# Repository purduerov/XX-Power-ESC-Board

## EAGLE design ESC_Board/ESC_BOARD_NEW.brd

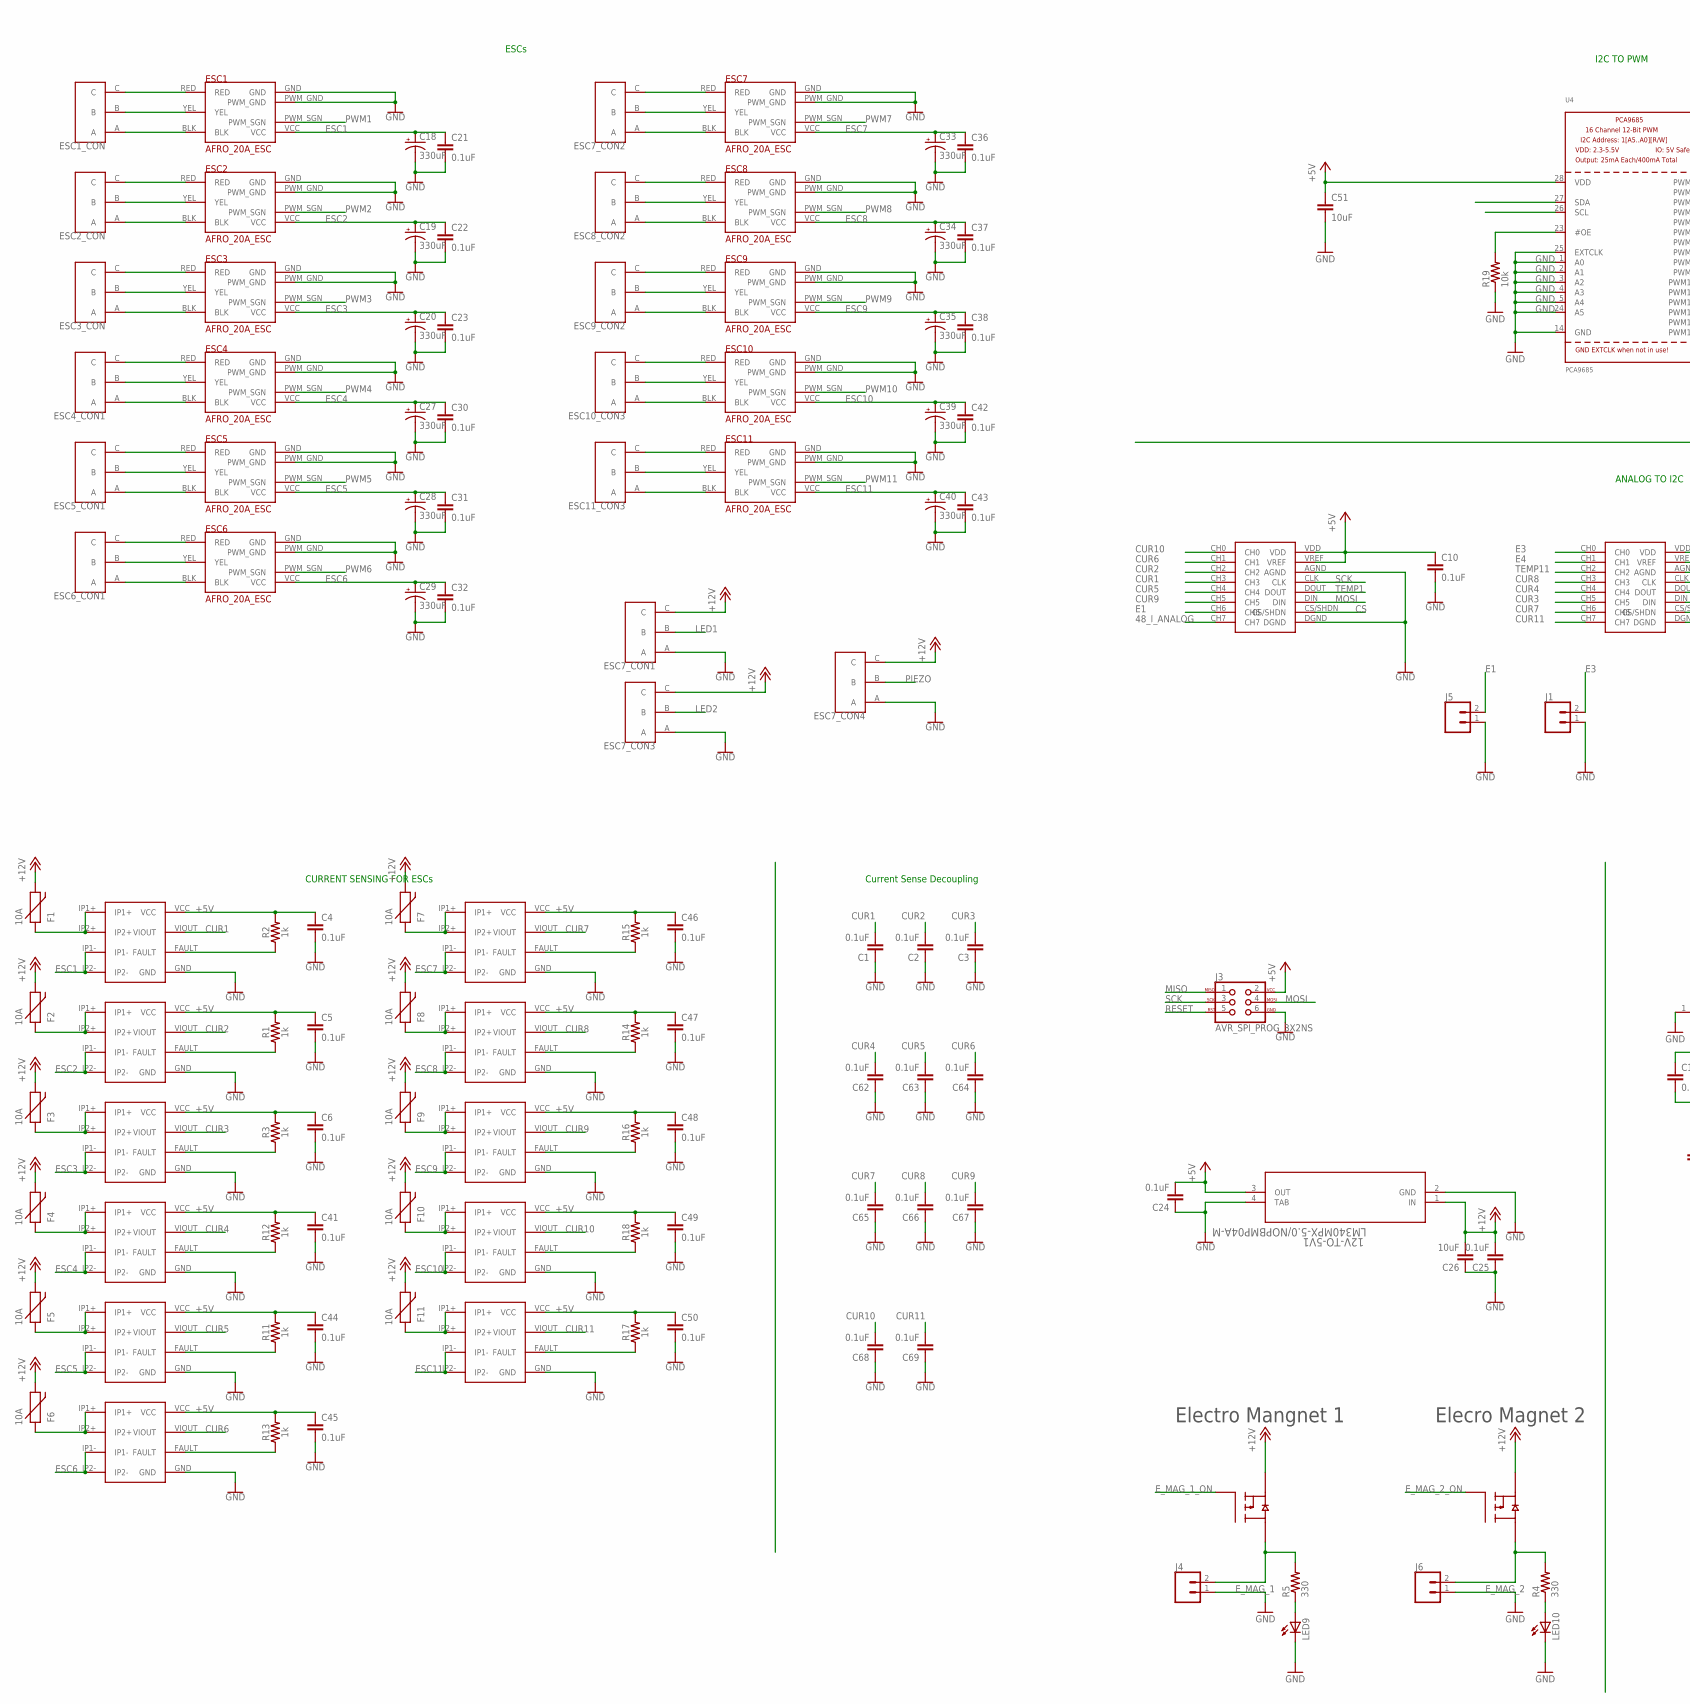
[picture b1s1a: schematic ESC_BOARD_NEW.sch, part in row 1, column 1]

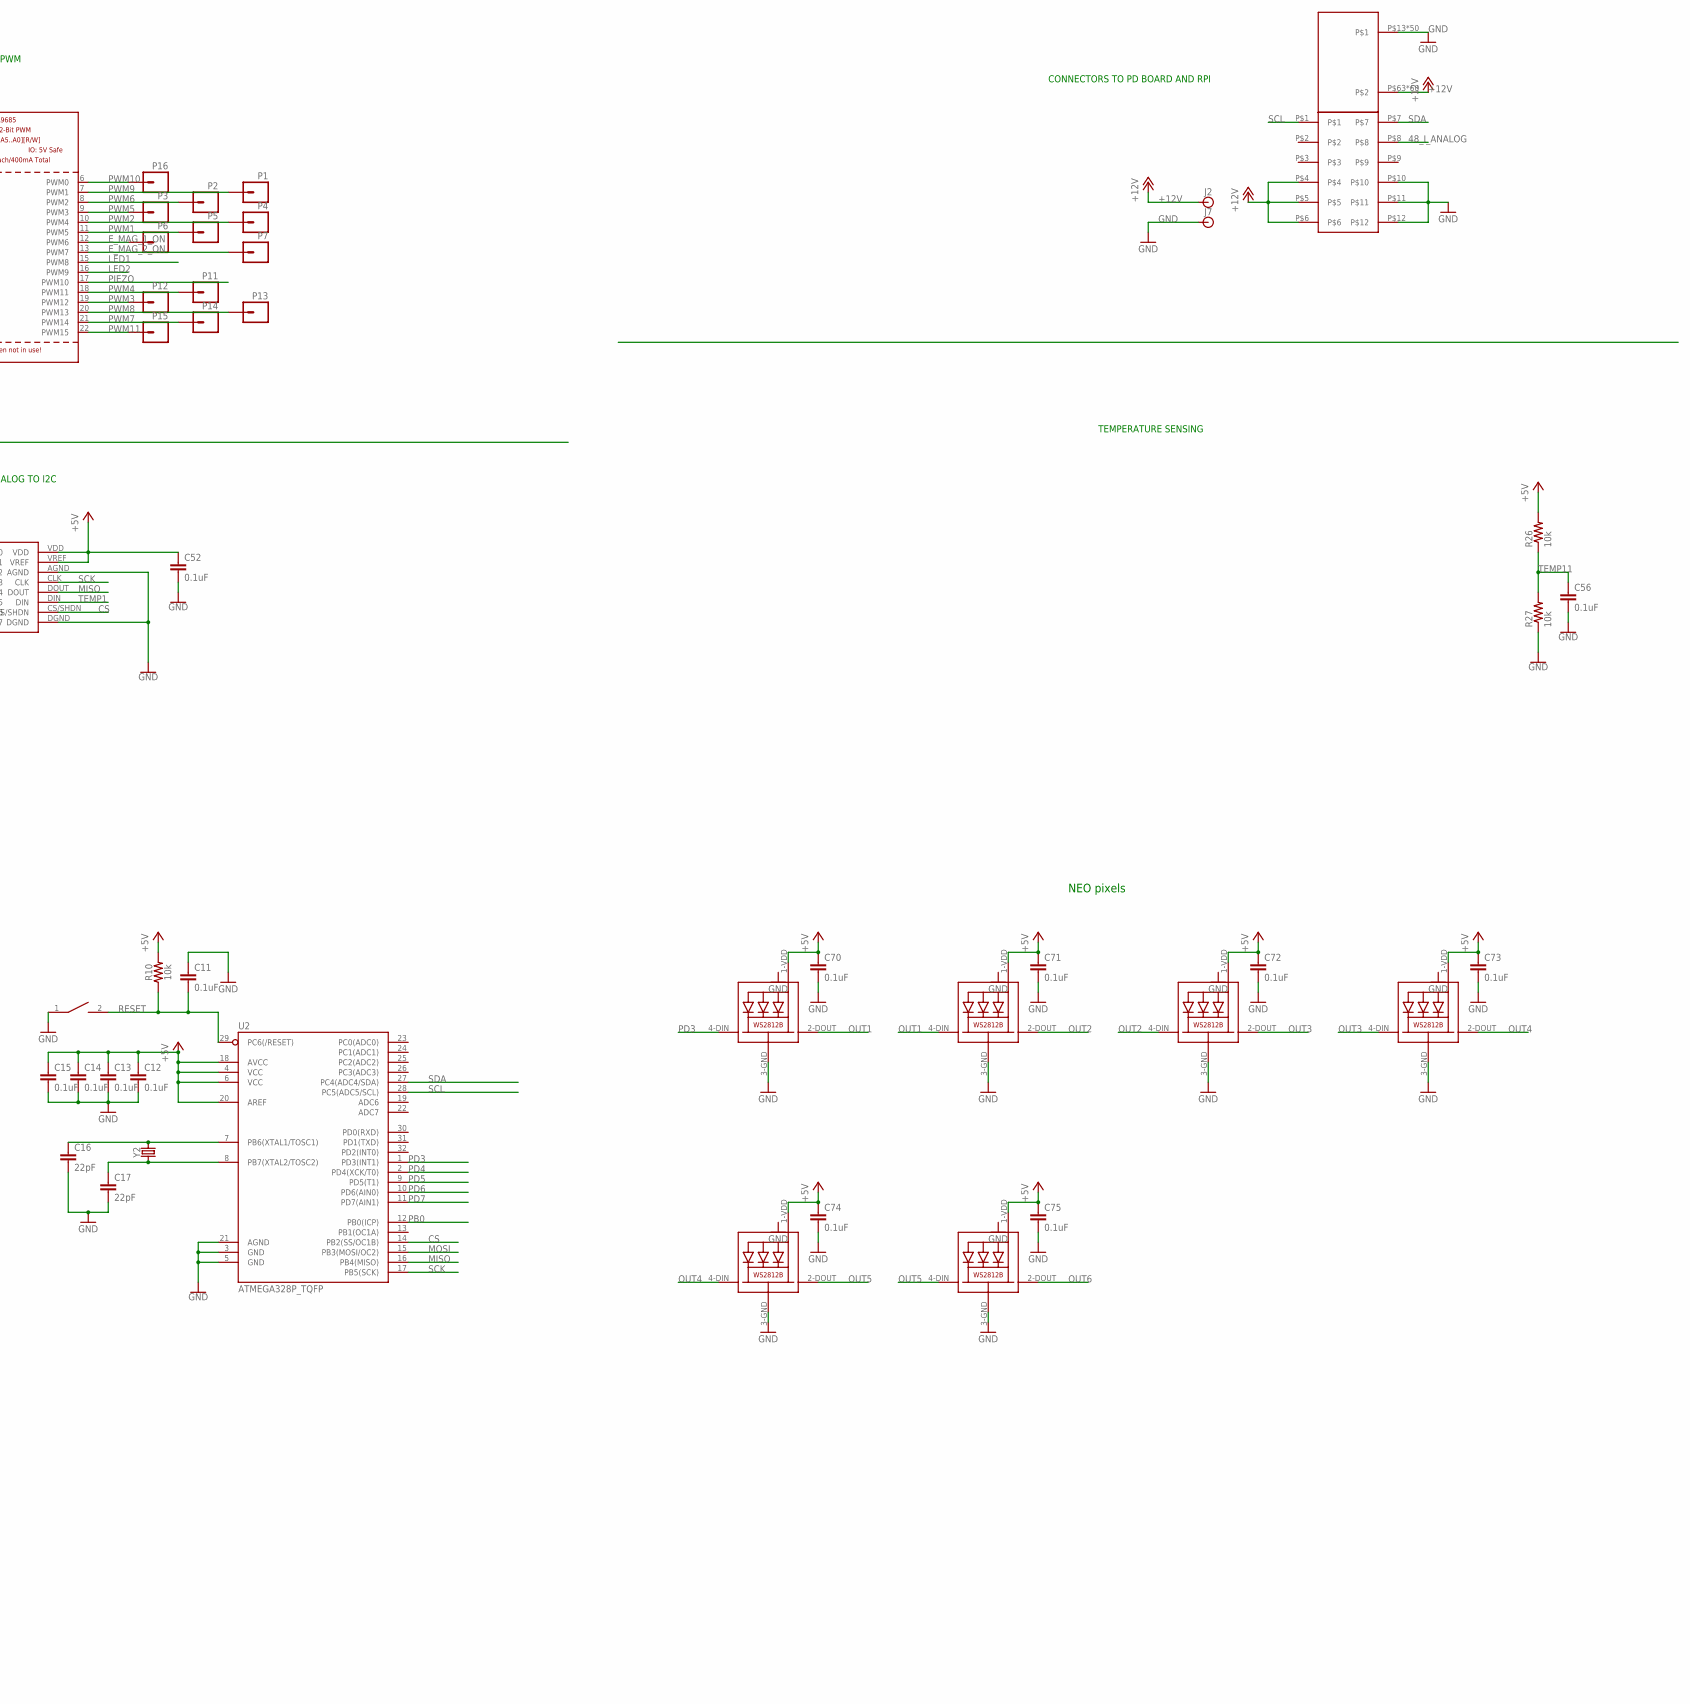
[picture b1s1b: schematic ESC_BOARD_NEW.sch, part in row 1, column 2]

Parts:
12V-TO-5V1: LM340MPX-5.0/NOPBMP04A-M; MP04A-M
C1, C2, C3, C4, C5, C6, C10, C21, C22, C23, C24, C25, C30, C31, C32, C36, C37, C38, C41, C42, C43, C44, C45, C46, C47, C48, C49, C50, C52, C56, C62, C63, C64, C65, C66, C67, C68, C69: 0.1uF; 0603
C11, C12, C13, C14, C15, C70, C71, C72, C73, C74, C75: 0.1uF; C0603
C16, C17: 22pF; C0603
C18, C19, C20, C27, C28, C29, C33, C34, C35, C39, C40: 330uF; CPOL-US(10.3_10.3MM)
C26: 10uF; 0603
C51: 10uF; 0603-CAP
ESC1, ESC2, ESC3, ESC4, ESC5, ESC6, ESC7, ESC8, ESC9, ESC10, ESC11: AFRO_20A_ESC
ESC1_CON, ESC2_CON, ESC3_CON, ESC4_CON1, ESC5_CON1, ESC6_CON1, ESC7_CON1, ESC7_CON2, ESC7_CON3, ESC7_CON4, ESC8_CON2, ESC9_CON2, ESC10_CON3, ESC11_CON3: 3PINCONNECTOR
F1, F2, F3, F4, F5, F6, F7, F8, F9, F10, F11: 10A; PTC-2920
J1, J4, J5, J6: CONN_02; 1X02
J2, J7: BANANA_CONN
J3: AVR_SPI_PROG_3X2NS; 2X3-NS
LED1, LED2, LED3, LED4, LED5, LED6: WS2812B5050; WS2812B
LED9, LED10: LEDSML0603; SML0603
P1, P2, P3, P4, P5, P6, P7, P11, P12, P13, P14, P15, P16: M01PTH; 1X01
R1, R2, R3, R11, R12, R13, R14, R15, R16, R17, R18: 1k; 0603
R4, R5: 330; R0603
R10: 10k; 0603
R19: 10k; 0603-RES
R26, R27: 10k; R0603
RESET: SWITCH; SW_2512
U1, U3: FQB27P06; TO263-3
U2: ATMEGA328P_TQFP; TQFP32-08
U4: PCA9685; TSSOP28
U$1, U$2, U$3, U$5, U$6, U$7, U$8, U$9, U$10, U$11, U$12: ACS711
U$4, U$13: MCP3008
U$15: ESC-FULL
Y2: CRYSTALPTH-HC49US; HC49US

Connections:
48_I_ANALOG: U$4.CH7, U$15.P$8
+5V: 12V-TO-5V1.3 (OUT), C4.1, C5.1, C6.1, C10.1, C12.1, C13.1, C14.1, C15.1, C24.2, C41.1, C44.1, C45.1, C46.1, C47.1, C48.1, C49.1, C50.1, C51.1, C52.1, C70.1, C71.1, C72.1, C73.1, C74.1, C75.1, J3.2, LED1.1-VDD (VDD), LED2.1-VDD (VDD), LED3.1-VDD (VDD), LED4.1-VDD (VDD), LED5.1-VDD (VDD), LED6.1-VDD (VDD), R1.2, R2.2, R3.2, R10.2, R11.2, R12.2, R13.2, R14.2, R15.2, R16.2, R17.2, R18.2, R26.2, U2.4 (VCC), U2.6 (VCC), U2.18 (AVCC), U2.20 (AREF), U4.28 (VDD), U$1.VCC, U$2.VCC, U$3.VCC, U$4.VDD, U$4.VREF, U$5.VCC, U$6.VCC, U$7.VCC, U$8.VCC, U$9.VCC, U$10.VCC, U$11.VCC, U$12.VCC, U$13.VDD, U$13.VREF
+12V: 12V-TO-5V1.1 (IN), C25.2, C26.2, ESC7_CON1.C, ESC7_CON3.C, ESC7_CON4.C, F1.2, F2.2, F3.2, F4.2, F5.2, F6.2, F7.2, F8.2, F9.2, F10.2, F11.2, J2.P$1, U1.3 (S2), U3.3 (S2), U$15.P$4, U$15.P$5, U$15.P$6, U$15.P$63, U$15.P$64, U$15.P$65, U$15.P$66, U$15.P$67, U$15.P$68, U$15.P$69, U$15.P$70, U$15.P$71, U$15.P$72, U$15.P$73, U$15.P$74, U$15.P$75, U$15.P$76, U$15.P$77, U$15.P$78, U$15.P$79, U$15.P$80, U$15.P$81, U$15.P$82, U$15.P$83, U$15.P$84, U$15.P$85, U$15.P$86, U$15.P$87, U$15.P$88, U$15.P$89, U$15.P$90, U$15.P$91, U$15.P$92, U$15.P$101, U$15.P$102, U$15.P$103, U$15.P$104, U$15.P$105, U$15.P$106, U$15.P$107, U$15.P$108, U$15.P$109, U$15.P$110, U$15.P$111, U$15.P$112, U$15.P$113, U$15.P$114, U$15.P$115, U$15.P$116, U$15.P$117, U$15.P$118, U$15.P$119, U$15.P$120, U$15.P$121, U$15.P$122, U$15.P$123, U$15.P$124, U$15.P$125, U$15.P$126, U$15.P$127, U$15.P$128, U$15.P$129, U$15.P$130
CS: U2.14 (PB2(SS/OC1B)), U$4.CS/SHDN, U$13.CS/SHDN
CUR1: C1.2, U$1.VIOUT, U$4.CH3
CUR2: C2.2, U$2.VIOUT, U$4.CH2
CUR3: C3.2, U$3.VIOUT, U$13.CH5
CUR4: C62.2, U$5.VIOUT, U$13.CH4
CUR5: C63.2, U$4.CH4, U$6.VIOUT
CUR6: C64.2, U$4.CH1, U$7.VIOUT
CUR7: C65.2, U$8.VIOUT, U$13.CH6
CUR8: C66.2, U$9.VIOUT, U$13.CH3
CUR9: C67.2, U$4.CH5, U$10.VIOUT
CUR10: C68.2, U$4.CH0, U$11.VIOUT
CUR11: C69.2, U$12.VIOUT, U$13.CH7
E1: J5.2, U$4.CH6
E3: J1.2, U$13.CH0
E4: U$13.CH1
ESC1: C18.+, C21.1, ESC1.VCC, U$1.IP1-, U$1.IP2-
ESC2: C19.+, C22.1, ESC2.VCC, U$2.IP1-, U$2.IP2-
ESC3: C20.+, C23.1, ESC3.VCC, U$3.IP1-, U$3.IP2-
ESC4: C27.+, C30.1, ESC4.VCC, U$5.IP1-, U$5.IP2-
ESC5: C28.+, C31.1, ESC5.VCC, U$6.IP1-, U$6.IP2-
ESC6: C29.+, C32.1, ESC6.VCC, U$7.IP1-, U$7.IP2-
ESC7: C33.+, C36.1, ESC7.VCC, U$8.IP1-, U$8.IP2-
ESC8: C34.+, C37.1, ESC8.VCC, U$9.IP1-, U$9.IP2-
ESC9: C35.+, C38.1, ESC9.VCC, U$10.IP1-, U$10.IP2-
ESC10: C39.+, C42.1, ESC10.VCC, U$11.IP1-, U$11.IP2-
ESC11: C40.+, C43.1, ESC11.VCC, U$12.IP1-, U$12.IP2-
E_MAG_1: J4.2, R5.2, U1.TAB (D2)
E_MAG_1_ON: P6.1, U1.1 (G2), U4.12 (PWM6)
E_MAG_2: J6.2, R4.2, U3.TAB (D2)
E_MAG_2_ON: P7.1, U3.1 (G2), U4.13 (PWM7)
GND: 12V-TO-5V1.2 (GND), 12V-TO-5V1.4 (TAB), C1.1, C2.1, C3.1, C4.2, C5.2, C6.2, C10.2, C11.1, C12.2, C13.2, C14.2, C15.2, C16.2, C17.2, C18.-, C19.-, C20.-, C21.2, C22.2, C23.2, C24.1, C25.1, C26.1, C27.-, C28.-, C29.-, C30.2, C31.2, C32.2, C33.-, C34.-, C35.-, C36.2, C37.2, C38.2, C39.-, C40.-, C41.2, C42.2, C43.2, C44.2, C45.2, C46.2, C47.2, C48.2, C49.2, C50.2, C51.2, C52.2, C56.2, C62.1, C63.1, C64.1, C65.1, C66.1, C67.1, C68.1, C69.1, C70.2, C71.2, C72.2, C73.2, C74.2, C75.2, ESC1.GND, ESC1.PWM_GND, ESC2.GND, ESC2.PWM_GND, ESC3.GND, ESC3.PWM_GND, ESC4.GND, ESC4.PWM_GND, ESC5.GND, ESC5.PWM_GND, ESC6.GND, ESC6.PWM_GND, ESC7.GND, ESC7.PWM_GND, ESC7_CON1.A, ESC7_CON3.A, ESC7_CON4.A, ESC8.GND, ESC8.PWM_GND, ESC9.GND, ESC9.PWM_GND, ESC10.GND, ESC10.PWM_GND, ESC11.GND, ESC11.PWM_GND, J1.1, J3.6, J4.1, J5.1, J6.1, J7.P$1, LED1.3-GND (GND), LED2.3-GND (GND), LED3.3-GND (GND), LED4.3-GND (GND), LED5.3-GND (GND), LED6.3-GND (GND), LED9.C, LED10.C, R19.1, R27.1, RESET.1, U2.3 (GND), U2.5 (GND), U2.21 (AGND), U4.1 (A0), U4.2 (A1), U4.3 (A2), U4.4 (A3), U4.5 (A4), U4.14 (GND), U4.24 (A5), U4.25 (EXTCLK), U$1.GND, U$2.GND, U$3.GND, U$4.AGND, U$4.DGND, U$5.GND, U$6.GND, U$7.GND, U$8.GND, U$9.GND, U$10.GND, U$11.GND, U$12.GND, U$13.AGND, U$13.DGND, U$15.P$10, U$15.P$11, U$15.P$12, U$15.P$13, U$15.P$14, U$15.P$15, U$15.P$16, U$15.P$17, U$15.P$18, U$15.P$19, U$15.P$20, U$15.P$21, U$15.P$22, U$15.P$23, U$15.P$24, U$15.P$25, U$15.P$26, U$15.P$27, U$15.P$28, U$15.P$29, U$15.P$30, U$15.P$31, U$15.P$32, U$15.P$33, U$15.P$34, U$15.P$35, U$15.P$36, U$15.P$37, U$15.P$38, U$15.P$39, U$15.P$40, U$15.P$41, U$15.P$42, U$15.P$43, U$15.P$44, U$15.P$45, U$15.P$46, U$15.P$47, U$15.P$48, U$15.P$49, U$15.P$50, U$15.P$51, U$15.P$52, U$15.P$53, U$15.P$54, U$15.P$55, U$15.P$56, U$15.P$57, U$15.P$58, U$15.P$59, U$15.P$60, U$15.P$61, U$15.P$62
LED1: ESC7_CON1.B, U4.15 (PWM8)
LED2: ESC7_CON3.B, U4.16 (PWM9)
MISO: J3.1, U2.16 (PB4(MISO)), U$13.DOUT
MOSI: J3.4, U2.15 (PB3(MOSI/OC2)), U$4.DIN
unnamed: ESC2.RED, ESC2_CON.C
unnamed: R2.1, U$1.FAULT
unnamed: ESC2.YEL, ESC2_CON.B
unnamed: R1.1, U$2.FAULT
unnamed: ESC2.BLK, ESC2_CON.A
unnamed: R3.1, U$3.FAULT
unnamed: ESC1.RED, ESC1_CON.C
unnamed: ESC1.YEL, ESC1_CON.B
unnamed: ESC1.BLK, ESC1_CON.A
unnamed: ESC3.RED, ESC3_CON.C
unnamed: ESC3.YEL, ESC3_CON.B
unnamed: ESC3.BLK, ESC3_CON.A
unnamed: R12.1, U$5.FAULT
unnamed: C16.1, U2.7 (PB6(XTAL1/TOSC1)), Y2.2
unnamed: C17.1, U2.8 (PB7(XTAL2/TOSC2)), Y2.1
unnamed: ESC5.RED, ESC5_CON1.C
unnamed: ESC5.YEL, ESC5_CON1.B
unnamed: ESC5.BLK, ESC5_CON1.A
unnamed: ESC4.RED, ESC4_CON1.C
unnamed: ESC4.YEL, ESC4_CON1.B
unnamed: ESC4.BLK, ESC4_CON1.A
unnamed: ESC6.RED, ESC6_CON1.C
unnamed: ESC6.YEL, ESC6_CON1.B
unnamed: ESC6.BLK, ESC6_CON1.A
unnamed: ESC8.RED, ESC8_CON2.C
unnamed: ESC8.YEL, ESC8_CON2.B
unnamed: ESC8.BLK, ESC8_CON2.A
unnamed: ESC7.RED, ESC7_CON2.C
unnamed: ESC7.YEL, ESC7_CON2.B
unnamed: ESC7.BLK, ESC7_CON2.A
unnamed: ESC9.RED, ESC9_CON2.C
unnamed: ESC9.YEL, ESC9_CON2.B
unnamed: ESC9.BLK, ESC9_CON2.A
unnamed: ESC11.RED, ESC11_CON3.C
unnamed: ESC11.YEL, ESC11_CON3.B
unnamed: ESC11.BLK, ESC11_CON3.A
unnamed: ESC10.RED, ESC10_CON3.C
unnamed: ESC10.YEL, ESC10_CON3.B
unnamed: ESC10.BLK, ESC10_CON3.A
unnamed: R11.1, U$6.FAULT
unnamed: R13.1, U$7.FAULT
unnamed: R15.1, U$8.FAULT
unnamed: R14.1, U$9.FAULT
unnamed: R16.1, U$10.FAULT
unnamed: R18.1, U$11.FAULT
unnamed: R17.1, U$12.FAULT
unnamed: LED9.A, R5.1
unnamed: F6.1, U$7.IP1+, U$7.IP2+
unnamed: F1.1, U$1.IP1+, U$1.IP2+
unnamed: F2.1, U$2.IP1+, U$2.IP2+
unnamed: F3.1, U$3.IP1+, U$3.IP2+
unnamed: F4.1, U$5.IP1+, U$5.IP2+
unnamed: F5.1, U$6.IP1+, U$6.IP2+
unnamed: F7.1, U$8.IP1+, U$8.IP2+
unnamed: R19.2, U4.23 (#OE)
unnamed: F8.1, U$9.IP1+, U$9.IP2+
unnamed: F9.1, U$10.IP1+, U$10.IP2+
unnamed: F10.1, U$11.IP1+, U$11.IP2+
unnamed: F11.1, U$12.IP1+, U$12.IP2+
unnamed: LED10.A, R4.1
OUT1: LED1.2-DOUT (DO), LED2.4-DIN (DI)
OUT2: LED2.2-DOUT (DO), LED3.4-DIN (DI)
OUT3: LED3.2-DOUT (DO), LED4.4-DIN (DI)
OUT4: LED4.2-DOUT (DO), LED5.4-DIN (DI)
OUT5: LED5.2-DOUT (DO), LED6.4-DIN (DI)
OUT6: LED6.2-DOUT (DO)
PB0: U2.12 (PB0(ICP))
PD3: LED1.4-DIN (DI), U2.1 (PD3(INT1))
PD4: U2.2 (PD4(XCK/T0))
PD5: U2.9 (PD5(T1))
PD6: U2.10 (PD6(AIN0))
PD7: U2.11 (PD7(AIN1))
PIEZO: ESC7_CON4.B, U4.17 (PWM10)
PWM1: ESC1.PWM_SGN, P5.1, U4.11 (PWM5)
PWM2: ESC2.PWM_SGN, P4.1, U4.10 (PWM4)
PWM3: ESC3.PWM_SGN, P12.1, U4.19 (PWM12)
PWM4: ESC4.PWM_SGN, P11.1, U4.18 (PWM11)
PWM5: ESC5.PWM_SGN, P3.1, U4.9 (PWM3)
PWM6: ESC6.PWM_SGN, P2.1, U4.8 (PWM2)
PWM7: ESC7.PWM_SGN, P14.1, U4.21 (PWM14)
PWM8: ESC8.PWM_SGN, P13.1, U4.20 (PWM13)
PWM9: ESC9.PWM_SGN, P1.1, U4.7 (PWM1)
PWM10: ESC10.PWM_SGN, P16.1, U4.6 (PWM0)
PWM11: ESC11.PWM_SGN, P15.1, U4.22 (PWM15)
RESET: C11.2, J3.5, R10.1, RESET.2, U2.29 (PC6(/RESET))
SCK: J3.3, U2.17 (PB5(SCK)), U$4.CLK, U$13.CLK
SCL: U2.28 (PC5(ADC5/SCL)), U4.26 (SCL), U$15.P$1
SDA: U2.27 (PC4(ADC4/SDA)), U4.27 (SDA), U$15.P$7
TEMP1: U$4.DOUT, U$13.DIN
TEMP11: C56.1, R26.1, R27.2, U$13.CH2

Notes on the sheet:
CURRENT SENSING FOR ESCs
ESCs
Current Sense Decoupling
I2C TO PWM
ANALOG TO I2C
NEO pixels
CONNECTORS TO PD BOARD AND RPI
TEMPERATURE SENSING
Electro Mangnet 1
Elecro Magnet 2

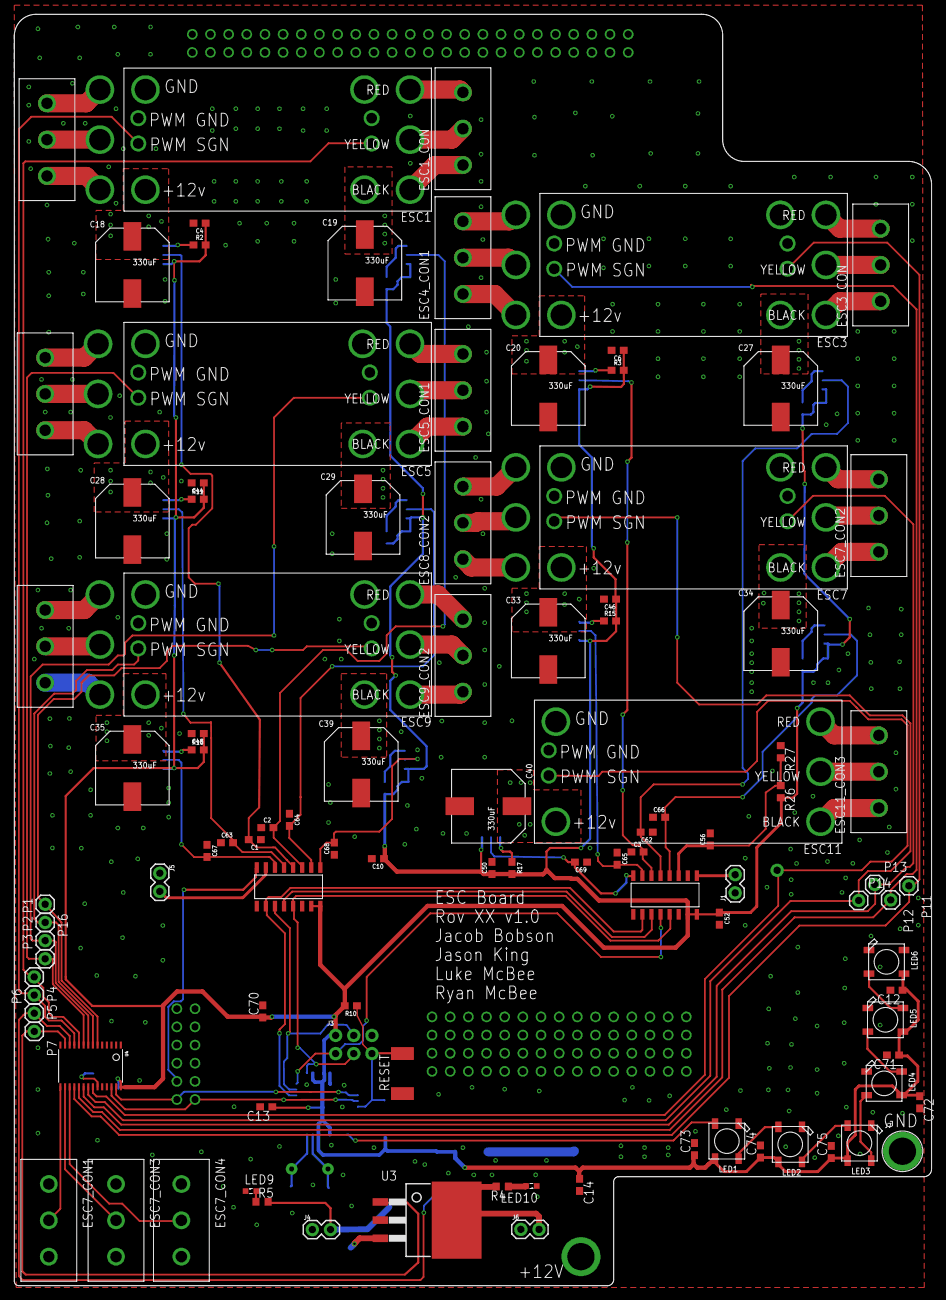
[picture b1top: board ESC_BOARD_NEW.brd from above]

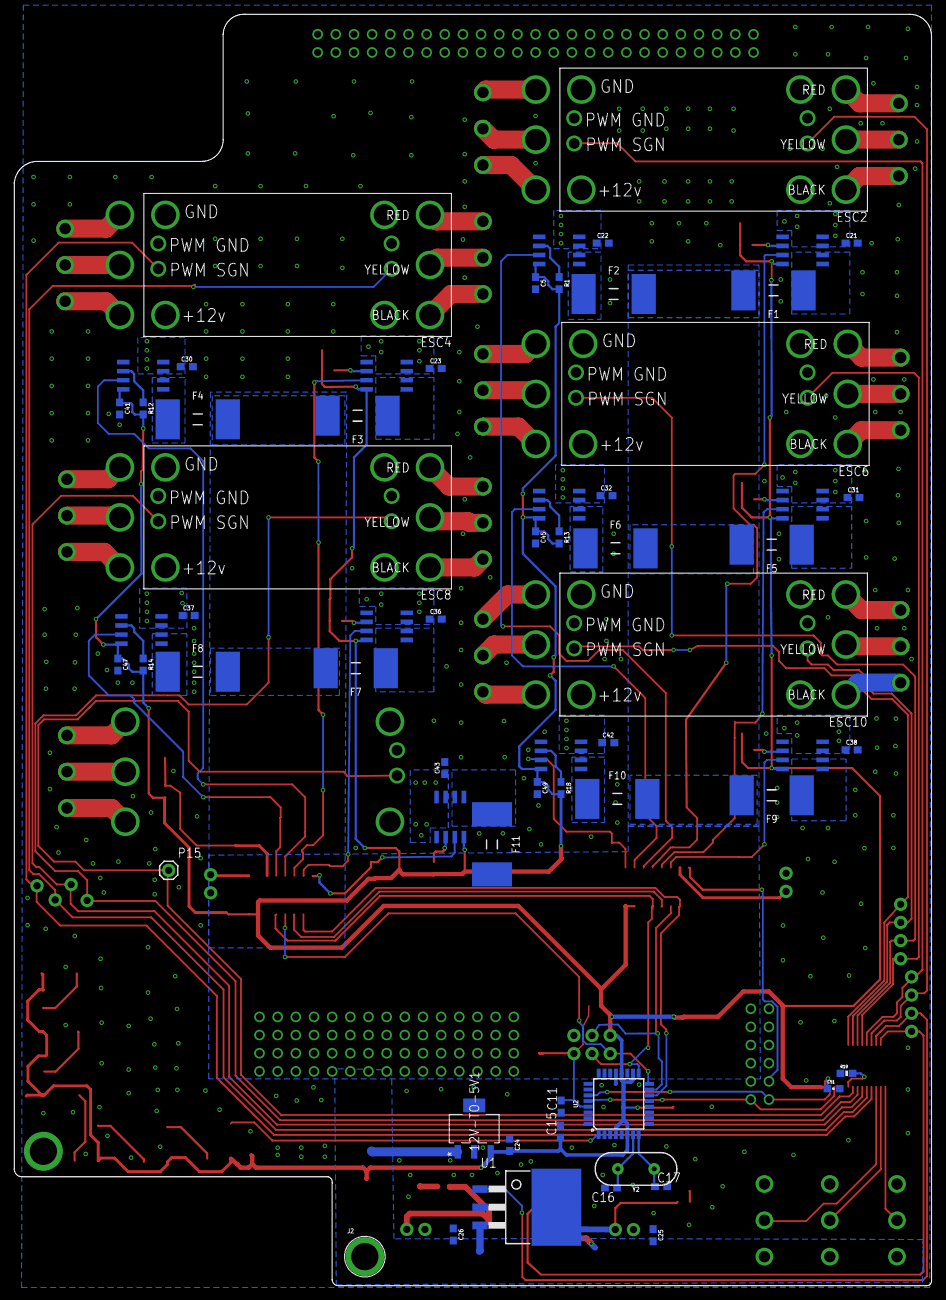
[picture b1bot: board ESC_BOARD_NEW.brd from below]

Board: 2 copper layers, 128.3 x 177.8 mm, 166 parts (63 on the bottom side), 121 nets.

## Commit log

2017-09-28 jason messing with things
2017-09-28 Created schematic file
2017-10-13 Added stuff from previous power conversion board
    added fuses and I2C to PWM circuitry
2017-10-15 Added gitignore
2017-10-15 Removed unnecessary temp files
2017-12-01 First Version of ESC Board
2017-12-02 More layout stuff
2017-12-08 Layout work
2017-12-14 Initial layout
2017-12-18 more board routing
2017-12-23 routing abomination in progress
2017-12-23 The fun continues
2017-12-24 Santa is dead and this board killed him
2017-12-24 How does that saying go? Trial by fire?
2017-12-27 God has abandoned us
2017-12-27 There is light at the end of the tunnel
2017-12-27 forgot schematic
2017-12-28 Thing and stuff done worked on
2017-12-28 There is hope
2017-12-28 More routing
2017-12-31 This might actually work
2017-12-31 GND is done messed up
2018-01-01 Finishing up first layout of parts for ESC board
2018-01-02 Added standard ESC to power distribution board connector
2018-01-03 Some final changes
2018-01-03 Added way to power electro magnets
2018-01-05 fixed up some of ground plane
2018-01-05 Fixing gnd plane and fixing traces
2018-01-07 Adding more test probes and cleaning up crooked traces
2018-01-08 Fixed to work with new part
2018-01-10 Version submitted to elecrow

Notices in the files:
parts and their libraries:
SparkFun-Capacitors: Licensing: Creative Commons ShareAlike 4.0 International - https://creativecommons.org/licenses/by-sa/4.0
